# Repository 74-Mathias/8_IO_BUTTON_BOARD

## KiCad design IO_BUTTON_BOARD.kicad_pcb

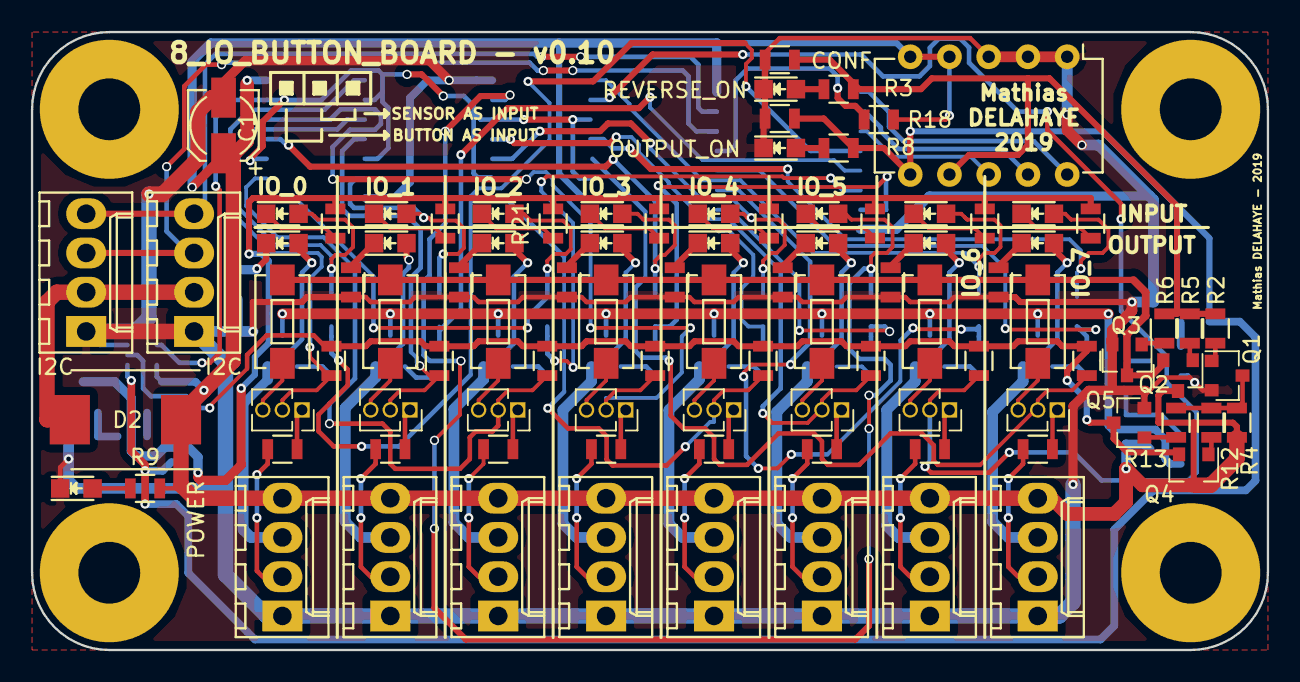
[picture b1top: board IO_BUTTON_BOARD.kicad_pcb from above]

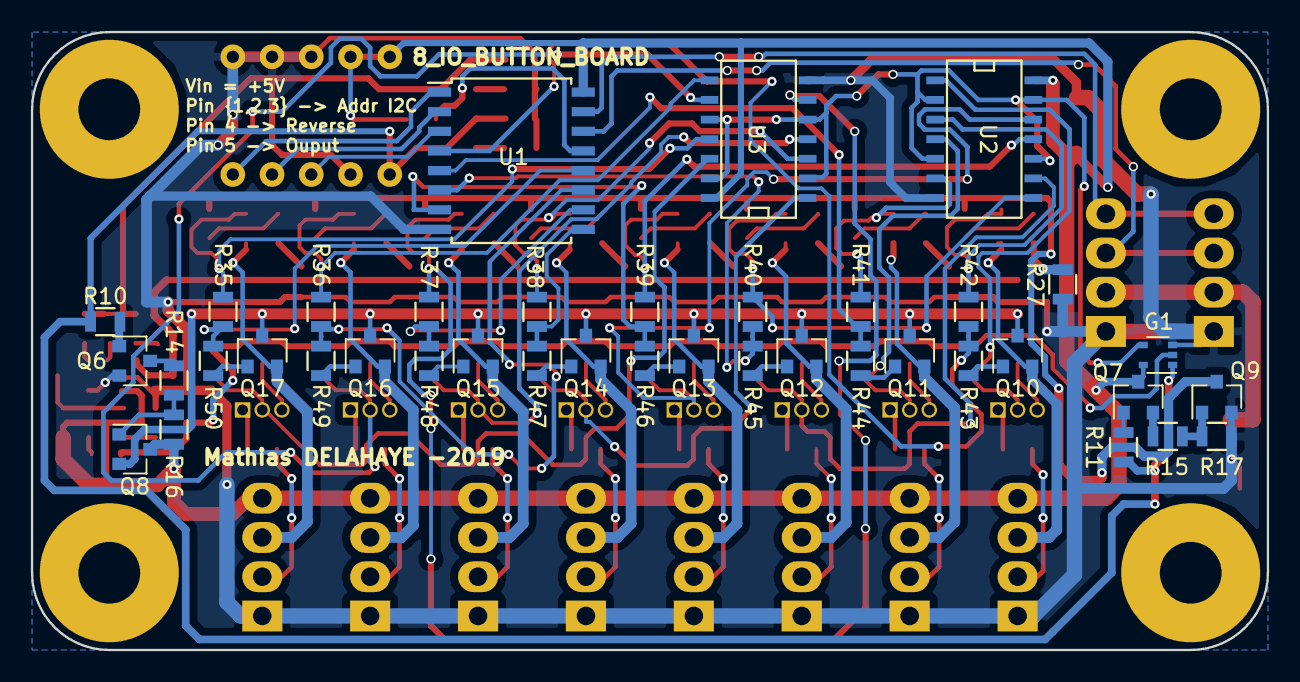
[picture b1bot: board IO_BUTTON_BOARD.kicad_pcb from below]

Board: 2 copper layers, 80.0 x 40.0 mm, 139 parts (39 on the bottom side), 111 nets.

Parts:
C1: 100n; c_elec_4x4.5
CONF: CONFIG; DIP-10_W7.62mm
D2: D; DO-214AB
D13: OUT_0; LED_0805
D14: OUT_1; LED_0805
D15: OUT_2; LED_0805
D16: OUT_3; LED_0805
D17: OUT_4; LED_0805
D18: OUT_5; LED_0805
D19: OUT_6; LED_0805
D20: OUT_7; LED_0805
G1: 74HC1G86GW; SOT-353
I2C, I2C#2: I2C; Molex_KK-6410-04_04x2.54mm_Straight
IO_0: SW_0; PinSocket_1x03_P1.27mm_Vertical
IO_0#2: IN_0; LED_0805
IO_1: SW_1; PinSocket_1x03_P1.27mm_Vertical
IO_1#2: IN_1; LED_0805
IO_2: SW_2; PinSocket_1x03_P1.27mm_Vertical
IO_2#2: IN_2; LED_0805
IO_3: SW_3; PinSocket_1x03_P1.27mm_Vertical
IO_3#2: IN_3; LED_0805
IO_4: SW_4; PinSocket_1x03_P1.27mm_Vertical
IO_4#2: IN_4; LED_0805
IO_5: SW_5; PinSocket_1x03_P1.27mm_Vertical
IO_5#2: IN_5; LED_0805
IO_6: SW_6; PinSocket_1x03_P1.27mm_Vertical
IO_6#2: IN_6; LED_0805
IO_7: SW_7; PinSocket_1x03_P1.27mm_Vertical
IO_7#2: IN_7; LED_0805
OUTPUT_ON: OUTPUT_MODE; LED_0805
P3: IO_0; Molex_KK-6410-04_04x2.54mm_Straight
P4: IO_1; Molex_KK-6410-04_04x2.54mm_Straight
P5: IO_2; Molex_KK-6410-04_04x2.54mm_Straight
P6: IO_3; Molex_KK-6410-04_04x2.54mm_Straight
P7: IO_4; Molex_KK-6410-04_04x2.54mm_Straight
P8: IO_5; Molex_KK-6410-04_04x2.54mm_Straight
P9: IO_6; Molex_KK-6410-04_04x2.54mm_Straight
P10: IO_7; Molex_KK-6410-04_04x2.54mm_Straight
POWER: POWER; LED_0805
Q1, Q3, Q5, Q6, Q9: NPN; SOT-23
Q2, Q4, Q7, Q8, Q10, Q11, Q12, Q13, Q14, Q15, Q16, Q17: PNP; SOT-23
R1, R3, R4, R7, R8, R9, R10, R14, R15, R19, R20, R21, R22, R23, R24, R25, R26, R27, R28, R29, R30, R31, R32, R33, R34, R35, R36, R37, R38, R39, R40, R41, R42, R51, R52, R53, R54, R55, R56, R57, R58, R59, R60, R61, R62, R63, R64, R65, R66: 1k; R_0805
R2, R5, R6, R11, R12, R13, R16, R17, R18, R43, R44, R45, R46, R47, R48, R49, R50: 10k; R_0805
REF01, REF02, REF03, REF04: MountingHole_4mm
REVERSE_ON: REVERSE; LED_0805
SW10, SW11, SW12, SW13, SW14, SW15, SW16, SW17: SW_Push; SW_SPST_EVQPE1
U1: PCF8574A; SOIC-16W_7.5x10.3mm_Pitch1.27mm
U2, U3: 74HC86; SOIC-14_N

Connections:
/ACTIVE_OUTPUT: CONF.6, G1.1, R7.1, R8.1, R10.1, R11.2
/CONTACT_LANE: Q2.2, Q3.3, SW10.2, SW11.2, SW12.2, SW13.2, SW14.2, SW15.2, SW16.2, SW17.2
/INPUT_LED_GND: Q9.3, R19.2, R20.2, R21.2, R22.2, R23.2, R24.2, R25.2, R26.2
/IN_0: P3.2, R59.2
/IN_1: P4.2, R60.2
/IN_2: P5.2, R61.2
/IN_3: P6.2, R62.2
/IN_4: P7.2, R63.2
/IN_5: P8.2, R64.2
/IN_6: P9.2, R65.2
/IN_7: P10.2, R66.2
/OUTPUT_VCC: Q8.2, Q10.3, Q11.3, Q12.3, Q13.3, Q14.3, Q15.3, Q16.3, Q17.3
/OUT_0: D13.2, P3.3, Q10.2
/OUT_1: D14.2, P4.3, Q11.2
/OUT_2: D15.2, P5.3, Q12.2
/OUT_3: D16.2, P6.3, Q13.2
/OUT_4: D17.2, P7.3, Q14.2
/OUT_5: D18.2, P8.3, Q15.2
/OUT_6: D19.2, P9.3, Q16.2
/OUT_7: D20.2, P10.3, Q17.2
/PULL_LANE: G1.2, Q4.2, Q5.3, R51.2, R52.2, R53.2, R54.2, R55.2, R56.2, R57.2, R58.2
/REF_XOR: G1.4, U2.2, U2.5, U2.10, U2.13, U3.2, U3.5, U3.10, U3.13
/REVERSE_PULL: CONF.7, R1.1, R2.2, R3.1, R5.1, R6.2
/SCL: I2C.3, I2C#2.3, U1.14
/SDA: I2C.4, I2C#2.4, U1.15
GND: C1.2, CONF.1, CONF.2, CONF.3, G1.3, I2C.1, I2C#2.1, OUTPUT_ON.1, P3.1, P4.1, P5.1, P6.1, P7.1, P8.1, P9.1, P10.1, POWER.1, Q1.2, Q3.2, Q5.2, Q6.2, Q9.2, R1.2, R7.2, R17.1, R27.2, R28.2, R29.2, R30.2, R31.2, R32.2, R33.2, R34.2, REVERSE_ON.1, U1.8, U2.7, U3.7
unnamed: R3.2, REVERSE_ON.2
unnamed: D2.2, I2C.2, I2C#2.2
unnamed: OUTPUT_ON.2, R8.2
unnamed: POWER.2, R9.2
unnamed: IO_0#2.1, R19.1
unnamed: IO_0#2.2, R42.2, U2.3
unnamed: IO_1#2.1, R20.1
unnamed: IO_1#2.2, R41.2, U2.6
unnamed: IO_2#2.1, R21.1
unnamed: IO_2#2.2, R40.2, U2.8
unnamed: IO_3#2.1, R22.1
unnamed: IO_3#2.2, R39.2, U2.11
unnamed: IO_4#2.1, R23.1
unnamed: IO_4#2.2, R38.2, U3.3
unnamed: IO_5#2.1, R24.1
unnamed: IO_5#2.2, R37.2, U3.6
unnamed: IO_6#2.1, R25.1
unnamed: IO_6#2.2, R36.2, U3.8
unnamed: IO_7#2.1, R26.1
unnamed: IO_7#2.2, R35.2, U3.11
unnamed: D13.1, R27.1
unnamed: D14.1, R28.1
unnamed: D15.1, R29.1
unnamed: D16.1, R30.1
unnamed: D17.1, R31.1
unnamed: D18.1, R32.1
unnamed: D19.1, R33.1
unnamed: D20.1, R34.1
unnamed: Q1.1, R2.1
unnamed: Q1.3, R4.2, R12.2, R13.1
unnamed: Q2.1, R5.2
unnamed: Q3.1, R6.1
unnamed: Q4.1, R12.1
unnamed: Q5.1, R13.2
unnamed: Q6.1, R10.2
unnamed: Q6.3, R14.2
unnamed: Q7.1, R11.1
unnamed: Q7.2, R15.2
unnamed: Q8.1, R14.1, R16.1
unnamed: Q9.1, R15.1, R17.2
unnamed: Q10.1, R43.1
unnamed: Q11.1, R44.1
unnamed: Q12.1, R45.1
unnamed: Q13.1, R46.1
unnamed: Q14.1, R47.1
unnamed: Q15.1, R48.1
unnamed: Q16.1, R49.1
unnamed: Q17.1, R50.1
unnamed: R18.1, U1.13
unnamed: R35.1, R50.2, U1.12
unnamed: R36.1, R49.2, U1.11
unnamed: R37.1, R48.2, U1.10
unnamed: R38.1, R47.2, U1.9
unnamed: R39.1, R46.2, U1.7
unnamed: R40.1, R45.2, U1.6
unnamed: R41.1, R44.2, U1.5
unnamed: R42.1, R43.2, U1.4
unnamed: IO_0.2, R51.1, U2.1
unnamed: IO_1.2, R52.1, U2.4
unnamed: IO_2.2, R53.1, U2.9
unnamed: IO_3.2, R54.1, U2.12
unnamed: IO_4.2, R55.1, U3.1
unnamed: IO_5.2, R56.1, U3.4
unnamed: IO_6.2, R57.1, U3.9
unnamed: IO_7.2, R58.1, U3.12
unnamed: IO_0.1, R59.1
unnamed: IO_1.1, R60.1
unnamed: IO_2.1, R61.1
unnamed: IO_3.1, R62.1
unnamed: IO_4.1, R63.1
unnamed: IO_5.1, R64.1
unnamed: IO_6.1, R65.1
unnamed: IO_7.1, R66.1
unnamed: CONF.8, U1.3
unnamed: CONF.9, U1.2
unnamed: CONF.10, U1.1
unnamed: IO_0.3, SW10.1
unnamed: IO_1.3, SW11.1
unnamed: IO_2.3, SW12.1
unnamed: IO_3.3, SW13.1
unnamed: IO_4.3, SW14.1
unnamed: IO_5.3, SW15.1
unnamed: IO_6.3, SW16.1
unnamed: IO_7.3, SW17.1
VCC: C1.1, CONF.4, CONF.5, D2.1, G1.5, P3.4, P4.4, P5.4, P6.4, P7.4, P8.4, P9.4, P10.4, Q2.3, Q4.3, Q7.3, Q8.3, R4.1, R9.1, R16.2, R18.2, U1.16, U2.14, U3.14

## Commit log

2019-01-30 Initial version of IO_BOARD
2019-01-30 Add reverse possibilities for pull-ups lanes
2019-01-30 Add protection resistances Add logical gates to reverse logical signal Reduce number of leds
2019-02-04 Remove second connector
2019-02-13 Add switchs for input selection Add output PNP transistors Use Labels
2019-02-13 Fix lib issues and change name to 8_IO_BOARD
2019-02-14 Add reverse current protection, generate netlist, add footprints
2019-02-14 Add pcb
2019-02-21 Fix footprint for Q13 Place components on board
2019-02-22 First routed version of the pcb
2019-02-23 Replace regular pins with molex KK connectors => - replace connectors - reroute the pcb
2019-02-24 Change silk-screening of the PCB
2019-02-27 Change positions of components Add mounting holes footprints Rerouted PCB
2019-02-27 Fix VCC disconnected issue Rerouted with larger width
2019-03-04 Reroute PCB with 'fake' +5V and GND netlist in order to get different width for PCB tracks
2019-03-04 Change silkscreen layout and 3D models
2019-03-05 Change positions and orientation of connectors on the pcb
2019-03-06 Fix missing pull resistor Reroute PCB
2019-03-06 Change marking
2019-03-06 Remove useless resistors Todo : develop a system to free XOR outputs on input mode
2019-03-07 Add switch to switch between Input and Ouput mode
2019-03-07 Change Schematic with full separation of alimentations
2019-03-07 Remove alimentation for OUTPUT leds as when the power lane of PNPs is off, leds cannot be turned on
2019-03-07 Add resistances to protect 74HC86 gates from inputs hazard
2019-03-07 Add footprints and some RS references
2019-03-07 Place mounting holes
2019-03-09 Add manual routing, XOR gates remains to be routed
2019-03-10 Add routing, logical tracks remains to be added
2019-03-10 Route completed
2019-03-10 Increased track width
2019-03-10 Edit silkscreen
